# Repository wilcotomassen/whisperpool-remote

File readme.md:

# Whisper Pool remote replacement

> TLDR: Whirlpool remote didn't work. I replaced it with an Arduino
> based remote that sent out the same [RC5](https://en.wikipedia.org/wiki/RC-5) remote 
> commands using this [Arduino IR-Remote library](https://github.com/z3t0/Arduino-IRremote).
>
> You can find the code [here](firmware) and the schematics and
> pcb design [here](hardware)
>
> I think this same solution should work for following whirlpools from Villeroy & Boch:
> 
> * Whisper Airpool
> * Clairpool
> * Whisper Whirlpool
> * Whisper Combipool

## The problem with the remote

Our home has a Villeroy and Boch whirlpool installed and after about half a 
year after we moved in and about three uses, the remote stopped functioning.

Opening the battery compartment made the cause cleary very quickly. The batteries
started leaking and (probably) deposited their acidic schmoo all over the pcb, 
corriding it and the components. As the remote enclosure is water proof and seems
to be glued together, there was no easy way to clean it. After trying to rinse it
out with some household chemicals through the battery compartment, it still didn't 
work.

There are replacement remotes availble, but they are about 150 euros. I like a 
working whirlpool, but not that much. So I decided to tear it down and see if there
was a likely fix.

## Teardown an protocol identification

There was no easy way to open the remote enclosure (because it's water proof), 
so I ended up cracking it open with pliers to get to in. Inside there's 
pretty much what one would expect, a tube to act as the battery compartment, a
small PCB in the middle doing the logic and an IR led to send the commands.

> As you can see there's quite a bit of corrosion on the PCB, either from moisture
> or from battery acid. Cleaning it with some isopropyl alcohol might salvage this, but
> I opted to toss it, rather that attempt that. The cut leads are from the IR led.

### RC5 transmitter IC

The main attraction on the PCB is the Philips/NXP IC, which is an RC5 Infrared 
remote control transmitter that does pretty much everything on the board. 

These markings are printet on the chip, next to the Philips logo:

> **SAA3010T**  
> **79030C**  
> **US0211 2 Y**  

The data sheet can be found [here](docs/SAA3010T-datasheet.pdf)

The chip handles the scanning of the remote buttons, and converting those into
valid [RC5 protocol](https://en.wikipedia.org/wiki/RC-5) commands and sending 
them out into the world via the IR led.

The [datasheet](SAA3010T-datasheet.pdf) explains how the key scan combinations
are converted into the RC5 address and command bits, so there's no code that
runs on the IC for this specific remote; all the information for the commands
is in the connections on the PCB (which is good, because I cannot capture the 
RC commands from a non-working remote).

### RC5 protocol parts

A command in the RC5 protocol is composed of 

* One start bit (fixed value of 1)
* One field bit (fixed value of 1)
* One control bit (toggled between commands)
* Five address bits (to set the system type, e.g. TV, VCR, etc)
* Six command bits (the actual command)

more information [here](https://en.wikipedia.org/wiki/RC-5)

We need to figure out the address and command bits to make a working
remote.

### Address bits

Finding the correct address bits was as simple as finding which Z- and 
DR lines from the IC were connected on the PCB. They turned out to be
Z3 (pin 6) and DR7 (pin 9). From the System matrix in the datasheet on
page 10, this dermines the system number 31 (a reserved system number), 
which has these system bits: ```11111```. 

### Command bits (via key scanning)

With a multimeter I checked how the buttons wires corresponded to the pins on the 
RC5 IC. It turns out that one wire was connected to the X5 pin and all the other
pins to 6 DR-lines.

When a buttons is pressed, it connects on of the DR pins to the X5 pin. The datasheet 
contains a nice table on page 9 to lookup the command bits for those X/DR combinations.

### Complete commands

| Button                                                 | Code | Start bit | Field bit | Control bit | Address bits | Command bits | => | Complete command | 
|--------------------------------------------------------|------|-----------|-----------|-------------|--------------|--------------|:--:|-----------------:|
|  | 40   | 1         | 1         | 1/0         | 11111        | 101000       | => | 11111111101000   |
|  | 41   | 1         | 1         | 1/0         | 11111        | 101001       | => | 11111111101001   |
|  | 42   | 1         | 1         | 1/0         | 11111        | 101010       | => | 11111111101010   |
|  | 43   | 1         | 1         | 1/0         | 11111        | 101011       | => | 11111111101011   |
|  | 44   | 1         | 1         | 1/0         | 11111        | 101100       | => | 11111111101100   |
|  | 45   | 1         | 1         | 1/0         | 11111        | 101101       | => | 11111111101101   |

## The replacement

Once the protocol was found, it was fairly easy to find an Arduino library that 
was able to send out RC5 commands: [Arduino IR-Remote](https://github.com/z3t0/Arduino-IRremote)

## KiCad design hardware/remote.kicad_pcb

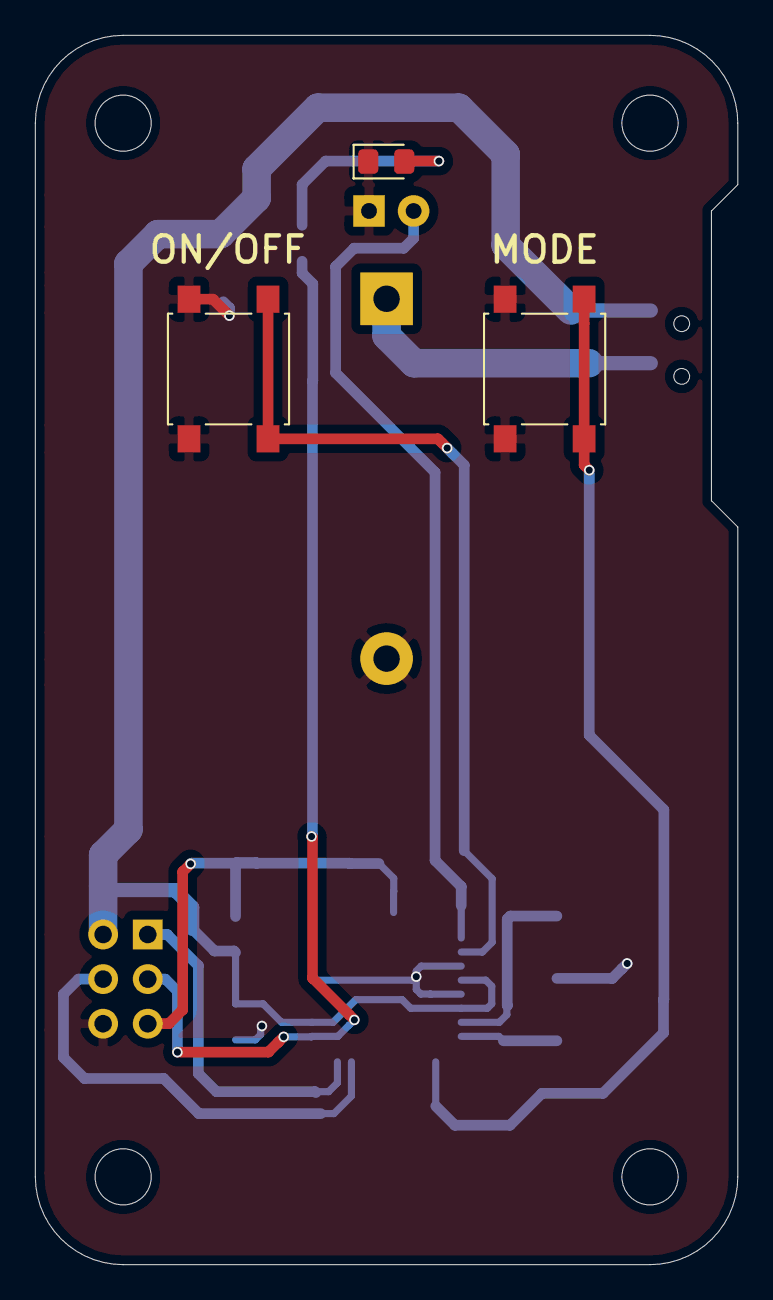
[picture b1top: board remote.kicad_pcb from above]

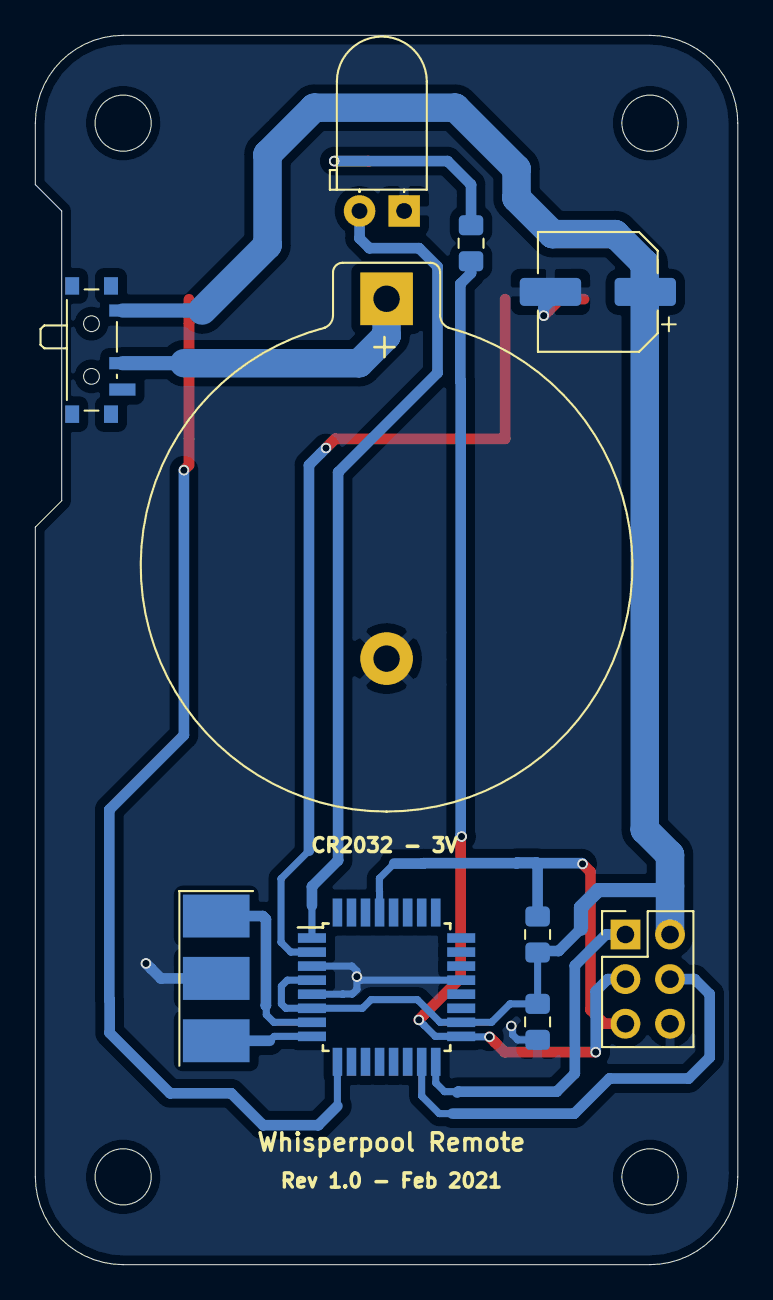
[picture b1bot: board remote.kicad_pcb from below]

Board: 2 copper layers, 40.0 x 70.0 mm, 17 parts (10 on the bottom side), 13 nets.

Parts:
BT1: Battery_Cell; BatteryHolder_Keystone_107_1x23mm
C1: C_Small; C_0805_2012Metric_Pad1.15x1.40mm_HandSolder
C2: CP_Small; CP_Elec_6.3x4.5
D1: LED; LED_D5.0mm_Horizontal_O1.27mm_Z3.0mm_IRBlack
D2: LED; LED_0805_2012Metric_Pad1.15x1.40mm_HandSolder
H1, H2, H3, H4: MountingHole; MountingHole_3.2mm_M3
J1: AVR-ISP-6; PinHeader_2x03_P2.54mm_Vertical
MODE: SW_Push; SW_SPST_B3S-1000
ON/OFF: SW_Push; SW_SPST_B3S-1000
R1, R2: R_Small; R_0805_2012Metric_Pad1.15x1.40mm_HandSolder
SW1: SW_SPDT; SW_SPDT_PCM12
U1: ATMEGA328-AU; TQFP-32_7x7mm_P0.8mm
Y1: Resonator_Small; Resonator_SMD-3Pin_7.2x3.0mm_HandSoldering

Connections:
BTN1: ON/OFF.2, U1.2
BTN2: MODE.2, U1.9
GND: BT1.2, C1.2, C2.2, D1.1, D2.1, J1.6, MODE.1, ON/OFF.1, U1.3, U1.5, U1.21, Y1.2
LED_INFO: J1.3, R1.2, U1.17
LED_IR: D1.2, U1.1
MISO: J1.1, U1.16
MOSI: J1.4, U1.15
unnamed: BT1.1, SW1.2
unnamed: D2.2, R1.1
unnamed: U1.7, Y1.1
unnamed: U1.8, Y1.3
RST: J1.5, R2.2, U1.29
VCC: C1.1, C2.1, J1.2, R2.1, SW1.1, U1.4, U1.6, U1.18

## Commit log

2018-01-18 Added readme and initial docs
2018-01-18 Fixed image link
2018-01-18 Fixed image size
2018-01-18 Update readme.md
    Fixed image size
2018-01-18 Update readme.md
    Fix indentation
2018-01-18 Update readme.md
    Fixed comment block
2018-01-18 Update teardown-and-protocol-identification.md
    Update on teardown
2018-01-18 Added images
2018-01-18 Updated pin
2018-01-18 Added button images
2018-01-18 Update teardown-and-protocol-identification.md
    Added address bits
2018-01-18 Update teardown-and-protocol-identification.md
    Added complete commands table
2018-01-18 Update teardown-and-protocol-identification.md
    Added images to command table
2018-04-21 Added kicad hardware design
2018-04-30 Initial firmware
2018-04-30 Cleaned up code, added fuses
2018-04-30 Merged docs
2018-04-30 Fixed readme links
2018-04-30 Added image files from original PCB
2018-04-30 Added original pcb images to the readme
2019-10-21 Update to Kicad 5
2021-07-27 Added platformio based firmware
2021-07-27 Hardware update
